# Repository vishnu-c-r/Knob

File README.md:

# SmartKnob Project

A **haptic feedback rotary knob** that uses a BLDC motor, a magnetic encoder, and a microcontroller to simulate dynamic resistance, detents, and end-stops. This repository contains the hardware schematics, firmware, and any software tooling needed to build a SmartKnob capable of providing programmable tactile feedback.

## Features

- **Brushless DC Motor (BLDC) Actuation**  
  Provides smooth, programmable torque for simulating detents, stops, and variable friction.
- **Magnetic Encoder**  
  High-resolution angle sensing ensures precise readings of knob position for responsive haptic effects.
- **Microcontroller-Based Control**  
  Real-time control loop to modulate motor torque based on the current knob position and configured haptic profile.
- **Configurable Haptic Profiles**  
  Switch between profiles like soft detents, hard stops, free spin, and others at runtime.
- **Integrated IMU (Optional)**  
  Measures orientation or additional movement data if advanced features are needed (e.g., inertia simulation).

## Hardware Overview

1. **Microcontroller**  
   - **ESP32-S3** (or your chosen MCU) running the main control loop, reading encoder data, and driving the motor driver via PWM signals.

2. **Motor Driver**  
   - **TMC6300** (or equivalent) controlling the 3-phase BLDC gimbal motor. Capable of precise torque modulation at low voltages.

3. **Magnetic Encoder**  
   - **AS5600** or similar to read the knob position.  
   - Offers contactless angle measurement with 12–14 bits of resolution.

4. **Motor**  
   - A gimbal-style BLDC motor (e.g., GB2208) for low cogging torque and smooth rotation.

5. **Power Supply**  
   - A 5V supply or battery pack, regulated down to 3.3V for the microcontroller.  
   - Make sure your motor driver supply is sized for peak current demands.

6. **Optional IMU**  
   - An MPU6050 or another IMU for advanced inertial-based haptic effects.

<!-- ## Firmware Structure

- **Encoder Reading**  
  Reads magnetic encoder via I2C/SPI to get current angle.  
- **Torque Control**  
  Uses PWM signals to drive the BLDC motor. Basic approach might be trapezoidal commutation or a custom approach; advanced setups can use FOC (Field-Oriented Control).  
- **Haptic Profiles**  
  Different modes (e.g., detents, end-stops, friction) defined in code. The firmware calculates desired torque based on the current angle and active profile.  
- **Main Loop**  
  Runs at a suitable update rate (e.g., 1–2 kHz) to read the angle, compute desired motor torque, and send PWM outputs to the motor driver.

<!-- ## Getting Started -->

<!-- 1. **Clone this repository**  
   ```bash
   git clone https://github.com/<your-username>/SmartKnob.git
   cd SmartKnob
   ```

2. **Hardware Assembly**  
   - Solder or assemble the PCB, including the motor driver, microcontroller, encoder, and any connectors.  
   - Mount the BLDC motor and magnet for the encoder so they align properly.

3. **Firmware Deployment**  
   - Open the firmware folder in your preferred IDE (e.g., PlatformIO, Arduino IDE).  
   - Adjust pin mappings in `config.h` for your specific wiring.  
   - Upload the firmware to your MCU.

4. **Configuration**  
   - In `config.h`, set motor parameters, encoder offsets, or other constants.  
   - If using an IMU, enable and configure it in `imu.h`.

5. **Testing**  
   - Power on the system and turn the knob.  
   - Observe motor feedback. If configured with a detent profile, you should feel discrete steps. --> 

## Usage

- **Change Haptic Mode**  
  By default, the firmware might start in free-spin. Use serial commands or a button (if implemented) to cycle through modes like detent, friction, or fixed end-stops.

- **Calibrate Encoder**  
  Ensure the knob is at a known reference angle if your system requires zero-position alignment. Some code might handle offset automatically.

- **Safety Notes**  
  - The motor driver can produce torque. Be cautious of pinch points.  
  - Avoid over-current situations by setting current limits if your driver supports it.

## Contributing

1. **Fork the repository** and create your branch from `main`.  
2. **Commit your changes** and push to your fork.  
3. **Open a Pull Request** detailing your modifications or improvements.

## License

This project is licensed under the [MIT License](LICENSE.md) — you are free to modify and distribute with attribution. See the LICENSE file for details.

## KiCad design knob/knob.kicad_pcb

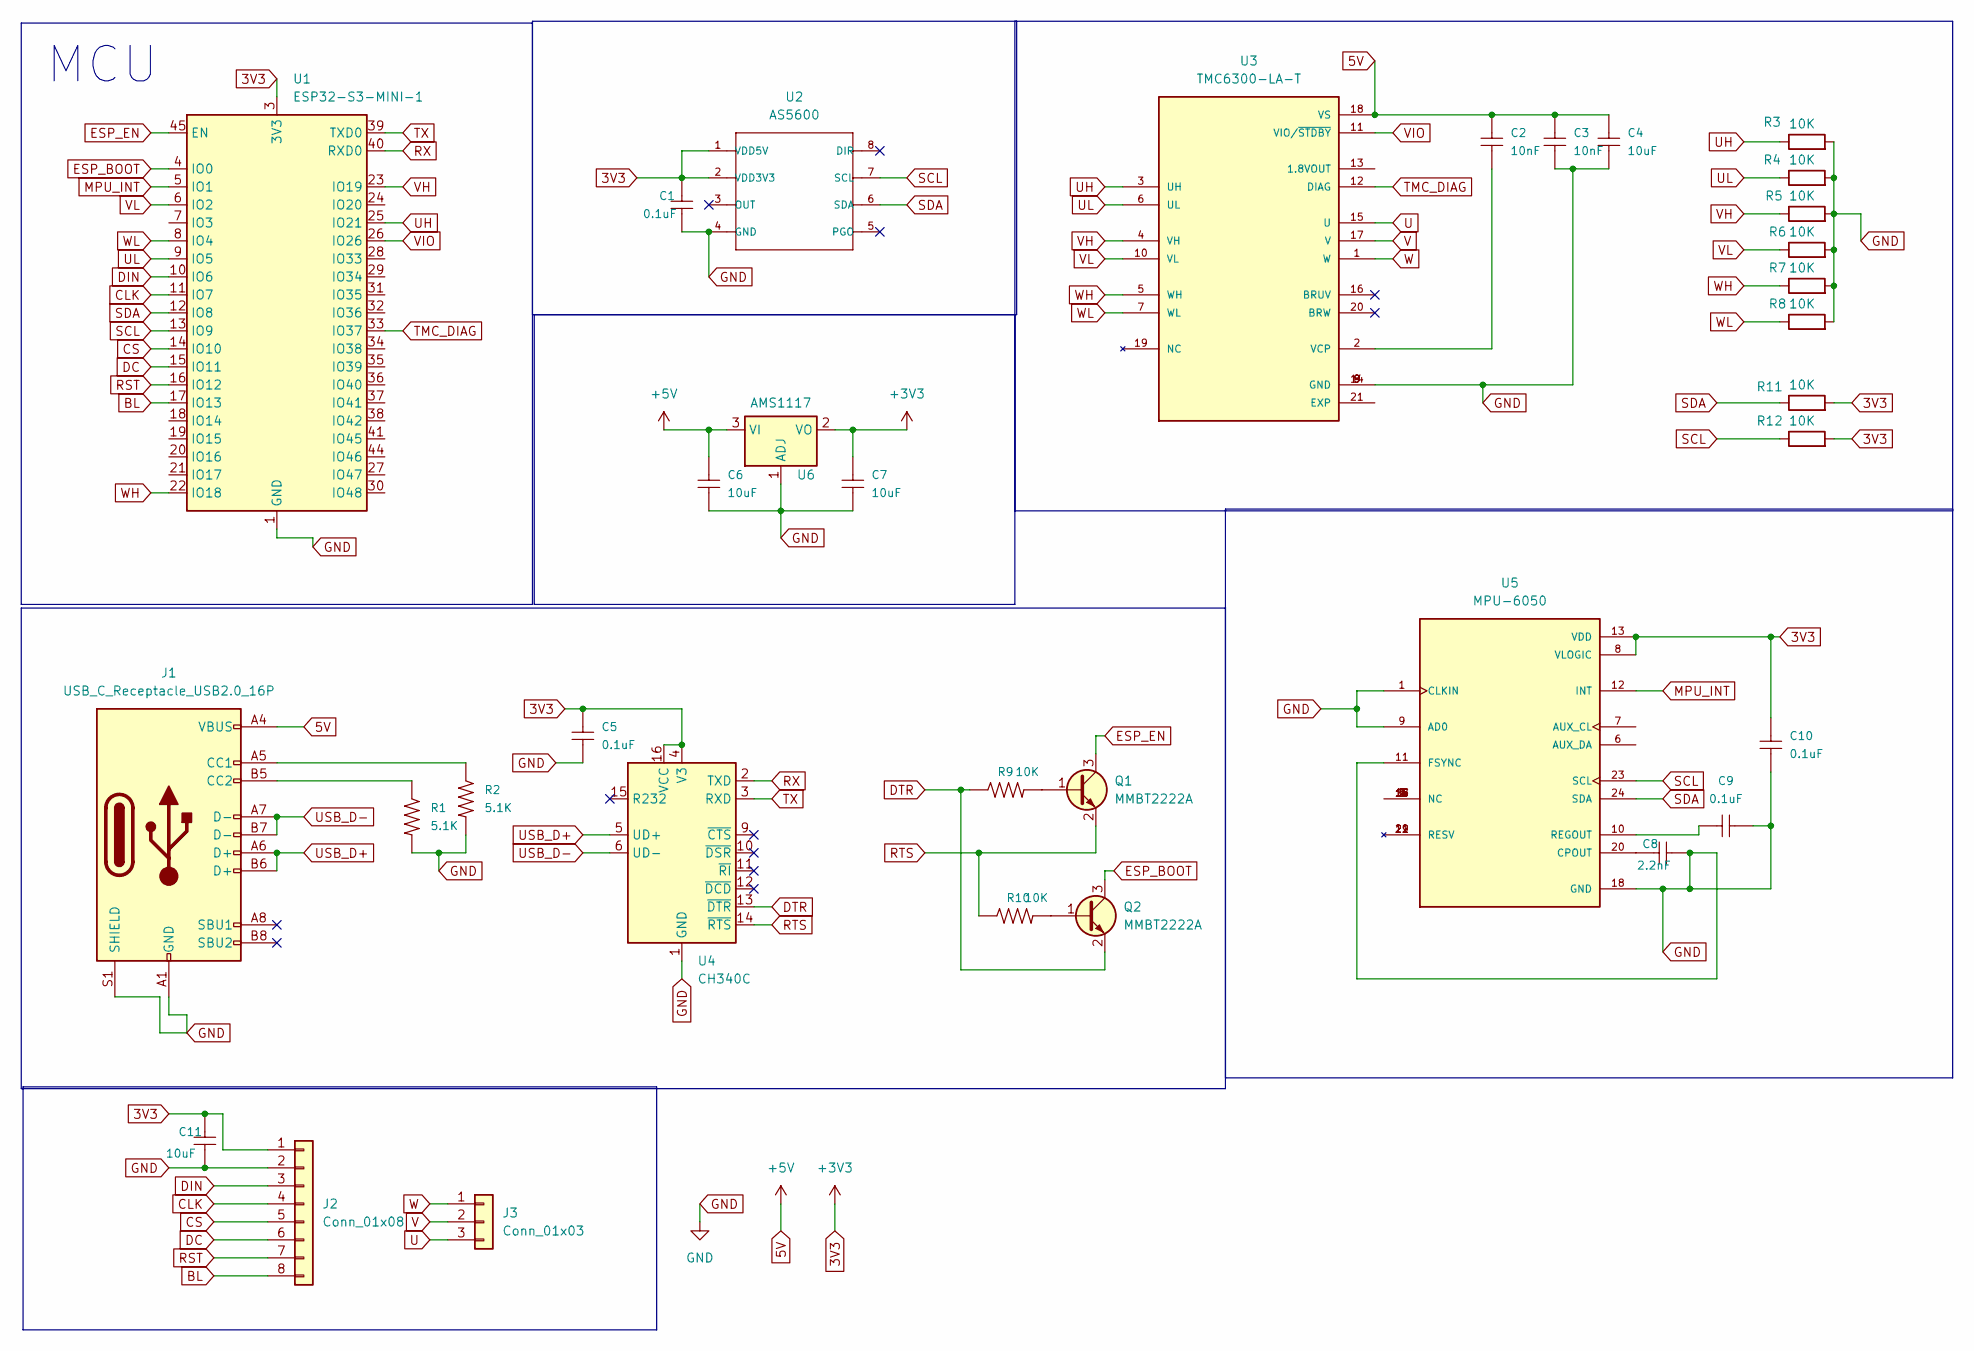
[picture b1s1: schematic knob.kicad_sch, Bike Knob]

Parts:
C1, C5, C9, C10: 0.1uF; C_0805_2012Metric
C2, C3: 10nF; C_0805_2012Metric
C4, C6, C7, C11: 10uF; C_0805_2012Metric
C8: 2.2nF; C_0805_2012Metric
J1: USB_C_Receptacle_USB2.0_16P; USB_C_Receptacle_GCT_USB4110
J2: Conn_01x08; PinSocket_1x08_P1.00mm_Vertical_SMD_Pin1Left
J3: Conn_01x03; JST_EH_S3B-EH_1x03_P2.50mm_Horizontal
Q1, Q2: MMBT2222A; SOT-23
R1, R2: 5.1K; R_0805_2012Metric_Pad1.20x1.40mm_HandSolder
R3, R4, R5, R6, R7, R8, R9, R10, R11, R12: 10K; R_0805_2012Metric_Pad1.20x1.40mm_HandSolder
U1: ESP32-S3-MINI-1; ESP32-S2-MINI-1
U2: AS5600
U3: TMC6300-LA-T; QFN40P300X300X90-21N; PARTREV 1.08
U4: CH340C; SOIC-16_3.9x9.9mm_P1.27mm
U5: MPU-6050; QFN50P400X400X95-24N; PARTREV 3.4
U6: AMS1117; SOT-223-3_TabPin2

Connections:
3V3: C1.2, C5.2, C7.2, C10.2, C11.2, J2.1, R11.2, R12.2, U1.3 (3V3), U2.1 (VDD5V), U2.2 (VDD3V3), U4.4 (V3), U4.16 (VCC), U5.8 (VLOGIC), U5.13 (VDD), U6.2 (VO)
5V: C2.2, C3.2, C4.2, C6.2, J1.A4 (VBUS), J1.A9 (VBUS), J1.B4 (VBUS), J1.B9 (VBUS), U3.18 (VS), U6.3 (VI)
BL: J2.8, U1.17 (IO13)
CLK: J2.4, U1.11 (IO7)
CS: J2.5, U1.14 (IO10)
DC: J2.6, U1.15 (IO11)
DIN: J2.3, U1.10 (IO6)
DTR: Q2.2 (E), R9.1, U4.13 (~DTR)
ESP_BOOT: Q2.3 (C), U1.4 (IO0)
ESP_EN: Q1.3 (C), U1.45 (EN)
GND: C1.1, C3.1, C4.1, C5.1, C6.1, C7.1, C8.1, C9.1, C10.1, C11.1, J1.A1 (GND), J1.A12 (GND), J1.B1 (GND), J1.B12 (GND), J1.S1 (SHIELD), J2.2, R1.2, R2.2, R3.2, R4.2, R5.2, R6.2, R7.2, R8.2, U1.1 (GND), U1.2 (GND), U1.42 (GND), U1.43 (GND), U1.46 (GND), U1.47 (GND), U1.48 (GND), U1.49 (GND), U1.50 (GND), U1.51 (GND), U1.52 (GND), U1.53 (GND), U1.54 (GND), U1.55 (GND), U1.56 (GND), U1.57 (GND), U1.58 (GND), U1.59 (GND), U1.60 (GND), U1.61 (GND), U1.62 (GND), U1.63 (GND), U1.64 (GND), U1.65 (GND), U2.4 (GND), U3.8 (VS), U3.9 (GND), U3.14 (GND), U4.1 (GND), U5.1 (CLKIN), U5.9 (AD0), U5.11 (FSYNC), U5.18 (GND), U6.1 (ADJ)
MPU_INT: U1.5 (IO1), U5.12 (INT)
unnamed: J1.A5 (CC1), R2.1
unnamed: J1.B5 (CC2), R1.1
unnamed: Q1.1 (B), R9.2
unnamed: Q2.1 (B), R10.2
unnamed: C2.1, U3.2 (VCP)
unnamed: C8.2, U5.20 (CPOUT)
unnamed: U5.2 (NC), U5.3 (NC), U5.4 (NC), U5.5 (NC), U5.14 (NC), U5.15 (NC), U5.16 (NC), U5.17 (NC)
unnamed: C9.2, U5.10 (REGOUT)
RST: J2.7, U1.16 (IO12)
RTS: Q1.2 (E), R10.1, U4.14 (~RTS)
RX: U1.40 (RXD0), U4.2 (TXD)
SCL: R12.1, U1.13 (IO9), U2.7 (SCL), U5.23 (SCL)
SDA: R11.1, U1.12 (IO8), U2.6 (SDA), U5.24 (SDA)
TMC_DIAG: U1.33 (IO37), U3.12 (DIAG)
TX: U1.39 (TXD0), U4.3 (RXD)
U: J3.3, U3.15 (U)
UH: R3.1, U1.25 (IO21), U3.3 (UH)
UL: R4.1, U1.9 (IO5), U3.6 (UL)
USB_D+: J1.A6 (D+), J1.B6 (D+), U4.5 (UD+)
USB_D-: J1.A7 (D-), J1.B7 (D-), U4.6 (UD-)
V: J3.2, U3.17 (V)
VH: R5.1, U1.23 (IO19), U3.4 (VH)
VIO: U1.26 (IO26), U3.11 (VIO/~STDBY)
VL: R6.1, U1.6 (IO2), U3.10 (VL)
W: J3.1, U3.1 (W)
WH: R7.1, U1.22 (IO18), U3.5 (WH)
WL: R8.1, U1.8 (IO4), U3.7 (WL)

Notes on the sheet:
MCU

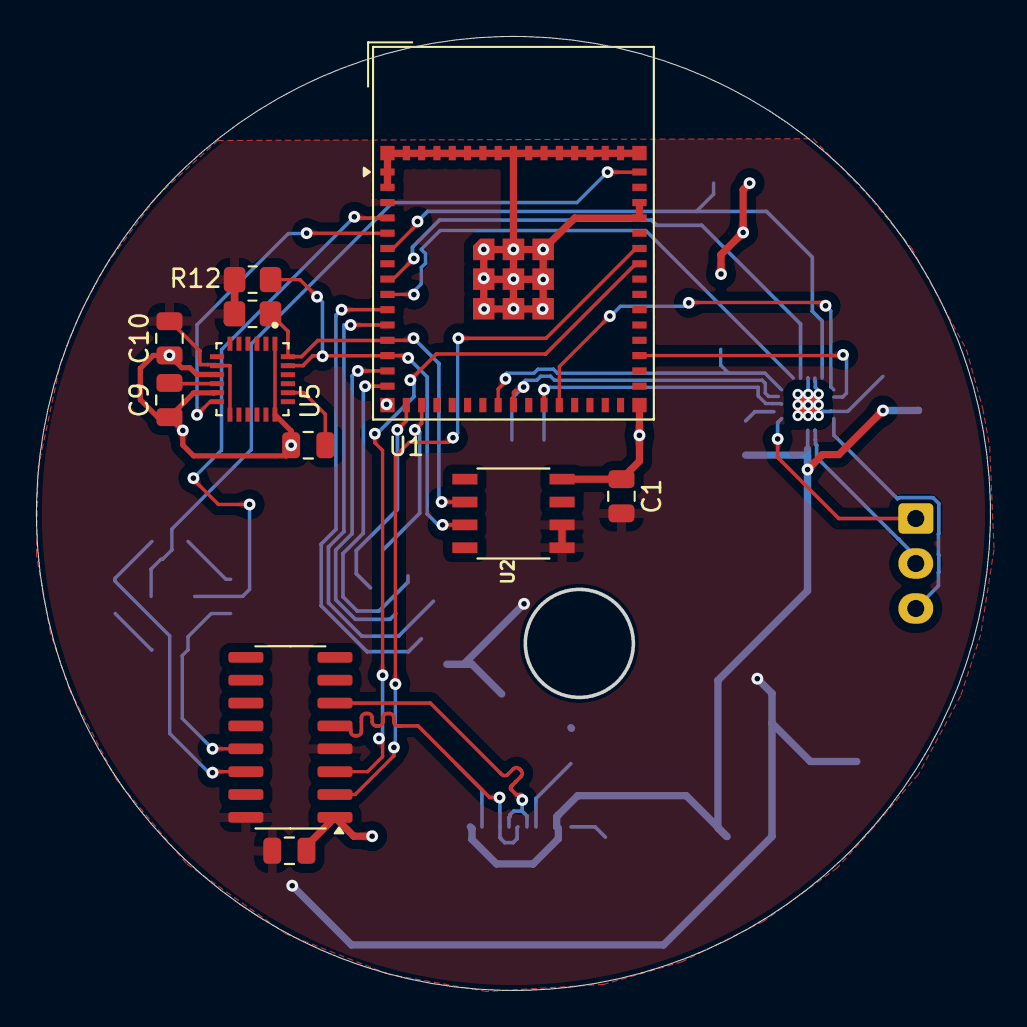
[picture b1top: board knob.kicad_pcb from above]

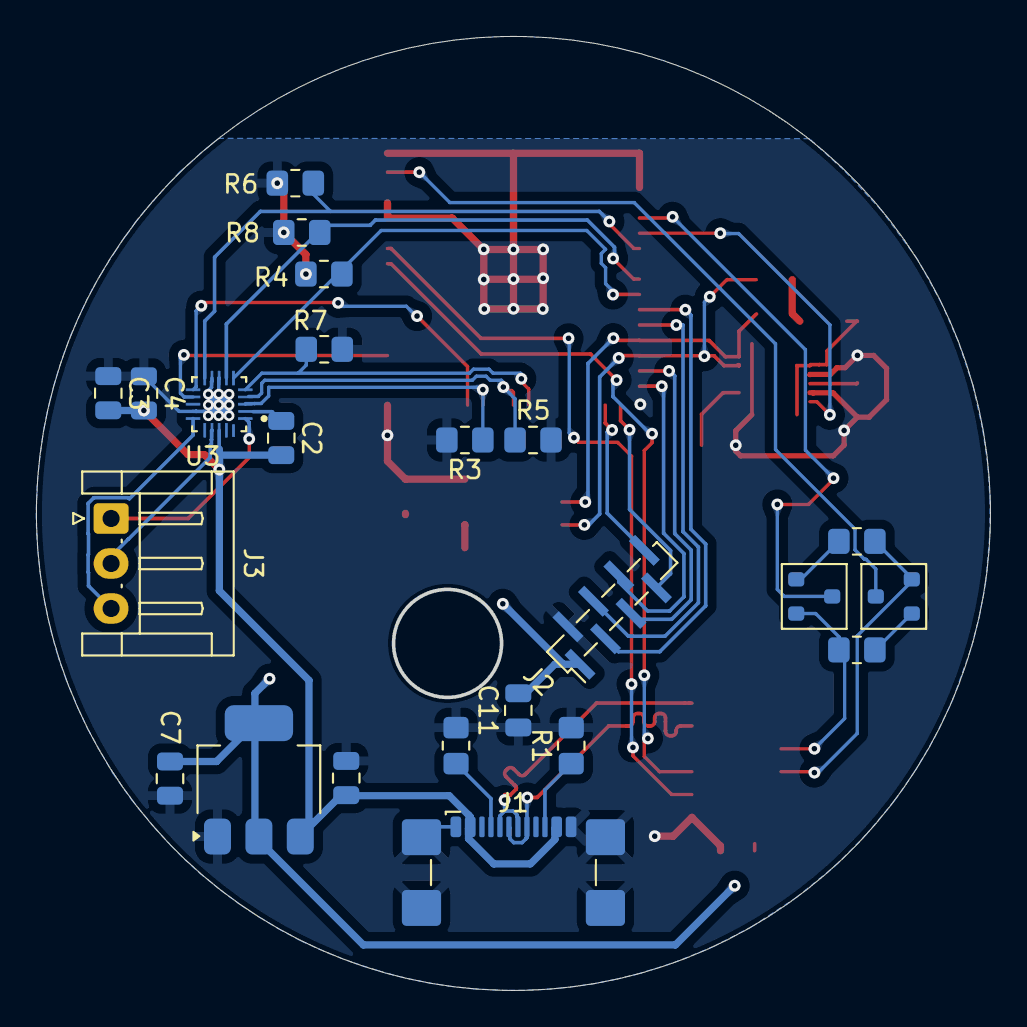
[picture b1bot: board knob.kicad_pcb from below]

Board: 2 copper layers, 52.9 x 52.9 mm, 34 parts (23 on the bottom side), 39 nets.

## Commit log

2025-01-29 initial prototype
2025-01-29 firmware files
2025-01-29 readme
2025-01-31 reordered files
